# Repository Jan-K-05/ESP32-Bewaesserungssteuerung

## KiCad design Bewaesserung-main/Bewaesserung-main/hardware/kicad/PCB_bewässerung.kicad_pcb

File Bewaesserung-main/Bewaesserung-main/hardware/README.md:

# Hardware und PCB-Entwicklung

## Grundlage
Schaltplan und Leiterplattenlayout der Bewässerungssteuerung wurden mit KiCad erstellt. Die folgende Bauteilübersicht basiert auf der Stückliste (CSV) des aktuellen Leiterplattenprojekts.

| Bauteil | Anzahl | Wert / Typ |
|---|---:|---|
| Mikrocontroller | 1 | DFRobot FireBeetle 2 ESP32-E |
| Leistungstransistoren Q1–Q8 | 8 | IRLZ44N |
| Freilaufdioden D1–D8 | 8 | 1N4007 |
| Gate-Widerstände | 8 | 300 Ω |
| Weitere Widerstände | 10 + 1 + 1 | 10 kΩ, 20 kΩ, 47 kΩ |
| DC/DC-Wandler | 1 | TRACO TSR2-2450N |
| Sicherung | 1 | 5 A |
| Puffer-/Entstörkondensatoren | 6 | 4 × 100 nF, 470 µF / 25 V, 100 µF / 10 V |

Die GPIO-Zuordnung der aktuellen Firmware ist in [firmware/bewaesserung.yaml](../firmware/bewaesserung.yaml) dokumentiert. Frühere Pinbelegungen entsprechen nicht mehr dem aktuellen Stand.

## Sensoren
- RS12-Regensensor: GPIO36, invertiertes Digitalsignal
- YF-B7-Durchflusssensor: GPIO35, Impulsmessung; derzeit 660 Impulse/L als Näherungswert
- NTC-Wassertemperatur: GPIO34, ADC mit Widerstands- und NTC-Umrechnung

## Bilddokumentation

KiCad-Schaltplan

Leiterplattenlayout

Teilbestückter Prototyp – Vorderseite

Leiterplattenrückseite – nachträgliche Anpassung des Regensensorsignals

## Bestückungsstand und Anpassung des Regensensors

Die gefertigte Leiterplatte ist bislang teilweise bestückt. Der FireBeetle-Controller ist montiert; Spannungsversorgung und Sensoranschlüsse sind aufgebaut. Von acht vorgesehenen Ventilstufen ist bislang eine bestückt. Die vollständige Bestückung und die Prüfung unter realen Wasserdrücken stehen noch aus, da die Gartenleitungen und Verteiler noch nicht fertiggestellt sind.

Regensensor RS12: Bei der Inbetriebnahme wurde festgestellt, dass das Ausgangsverhalten des Sensors von der in der Anleitung beschriebenen Open-Collector-Schaltung abweicht. Da diese Abweichung bei den ersten Tests nicht erkannt wurde, war eine Anpassung der bereits gefertigten Leiterplatte erforderlich. Dazu wurde auf der Leiterplattenrückseite ein zusätzlicher Widerstand zwischen Regensignal und GND angebracht. Die Pegelanpassung an den ESP32 erfolgt über einen Spannungsteiler. Die elektrische Funktion dieser Anpassung wurde erfolgreich geprüft. Der zusätzliche Widerstand ist als dauerhafte Lösung vorgesehen; eine erneute Fertigung der Leiterplatte ist derzeit nicht geplant. Die Änderung ist auf dem Foto der Leiterplattenrückseite erkennbar und wurde noch nicht in die KiCad-Dateien übernommen.

## Entwicklungsablauf
1. Anforderungen an die Bewässerungszonen und die Ventillasten festlegen
2. Schaltplan und Bauteilauswahl in KiCad ausarbeiten
3. Leiterplattenlayout für Leistungs- und Sensorsignale erstellen
4. Leiterplatte fertigen lassen, teilweise bestücken und elektrisch prüfen
5. Controller mit ESPHome und Home Assistant verbinden

## Noch ausstehende Arbeiten

- Die restlichen sieben Ventilstufen bestücken und prüfen
- Den Durchflusssensor unter realen Bedingungen kalibrieren
- Die Temperaturmessung kalibrieren
- Die dauerhaft vorgesehene Anpassung des Regensensors in den KiCad-Dateien dokumentieren
- Die gesamte Bewässerung nach Fertigstellung der Gartenleitungen hydraulisch testen
- Die geplanten lokalen Sicherheitsfunktionen ergänzen und erproben

Die geplante ESP-NOW-Verbindung zu einem zusätzlichen Waveshare-ESP mit Ethernet-Anschluss ist in der [Projektübersicht](../README.md) beschrieben. Sie ist noch nicht umgesetzt.

Die KiCad-Quelldateien liegen direkt unter [kicad/](kicad/), darunter [Projekt](kicad/PCB_bewässerung.kicad_pro), [Schaltplan](kicad/PCB_bewässerung.kicad_sch), [PCB-Layout](kicad/PCB_bewässerung.kicad_pcb), Symbol- und Footprint-Bibliotheken sowie die [Originalstückliste](kicad/PCB_bewässerung.csv). Eine ergänzende [vereinfachte Stückliste](kicad/PCB_bewaesserung_BOM.csv) ist ebenfalls enthalten.

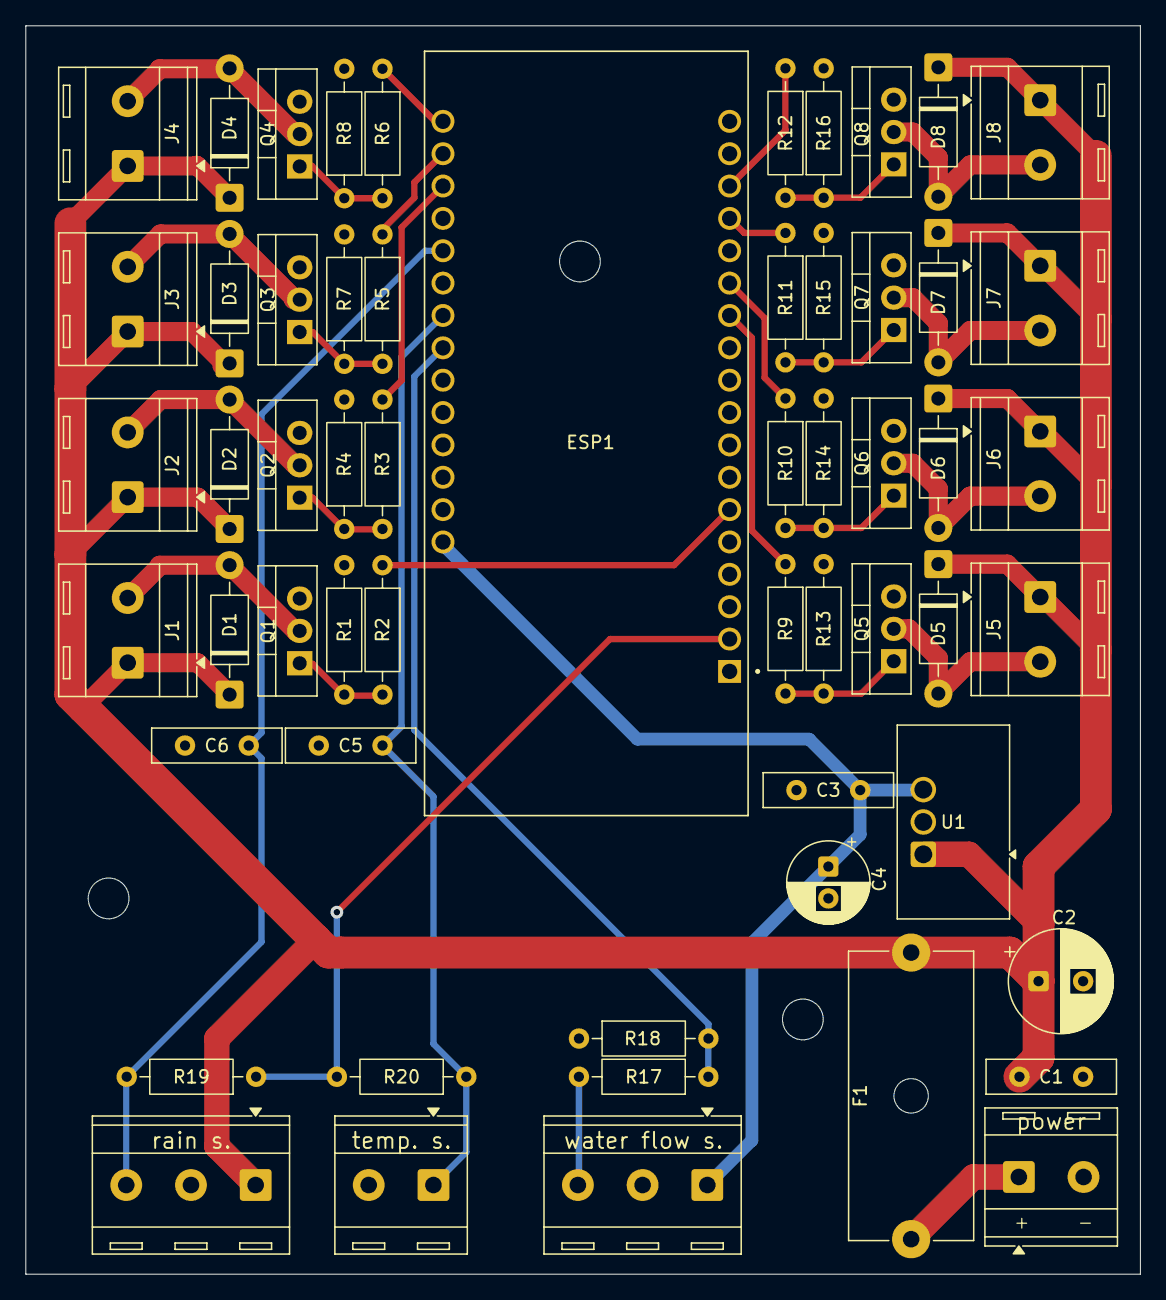
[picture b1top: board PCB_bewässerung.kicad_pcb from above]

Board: 2 copper layers, 87.5 x 98.0 mm, 57 parts (0 on the bottom side), 33 nets.

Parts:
C1, C3, C5, C6: 100nF; C_Disc_D10.0mm_W2.5mm_P5.00mm
C2: 470uF/25V; CP_Radial_D8.0mm_P3.50mm
C4: 100uF/10V; CP_Radial_D6.3mm_P2.50mm
D1, D2, D3, D4, D5, D6, D7, D8: 1N4007; D_DO-41_SOD81_P10.16mm_Horizontal
ESP1: DFR0654
F1: 5A; Fuseholder_Cylinder-5x20mm_Schurter_0031_8201_Horizontal_Op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
J1, J2, J3, J4, J5, J6, J7, J8, J9, J11: Screw_Terminal_01x02; TerminalBlock_RND_205-00287_1x02_P5.08mm_Horizontal
J12, J13: Screw_Terminal_01x03; TerminalBlock_RND_205-00288_1x03_P5.08mm_Horizontal
Q1, Q2, Q3, Q4, Q5, Q6, Q7, Q8: IRLZ44N; TO-220-3_Vertical
R1, R4, R7, R8, R13, R14, R15, R16, R19: 10kR; R_Axial_DIN0207_L6.3mm_D2.5mm_P10.16mm_Horizontal
R2, R3, R5, R6, R9, R10, R11, R12: 300R; R_Axial_DIN0207_L6.3mm_D2.5mm_P10.16mm_Horizontal
R17: 51kR; R_Axial_DIN0207_L6.3mm_D2.5mm_P10.16mm_Horizontal
R18: 68kR; R_Axial_DIN0207_L6.3mm_D2.5mm_P10.16mm_Horizontal
R20: 47kR; R_Axial_DIN0207_L6.3mm_D2.5mm_P10.16mm_Horizontal
U1: TSR2-2450N; Converter_DCDC_TRACO_TSR2-24xxN_TSR2-24xxxN_THT

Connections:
/3V3: ESP1.2 (3V3), R19.1, R20.2
/5V: C3.1, C4.1, ESP1.32 (VCC), J13.1, U1.3 (Vout)
/12V: C1.1, C2.1, D1.1 (K), D2.1 (K), D3.1 (K), D4.1 (K), D5.1 (K), D6.1 (K), D7.1 (K), D8.1 (K), F1.1, J1.1, J2.1, J3.1, J4.1, J5.1, J6.1, J7.1, J8.1, J12.1, U1.1 (Vin)
GND: C1.2, C2.2, C3.2, C4.2, C5.1, C6.1, ESP1.30 (GND), J9.2, J11.2, J12.2, J13.2, Q1.3 (S), Q2.3 (S), Q3.3 (S), Q4.3 (S), Q5.3 (S), Q6.3 (S), Q7.3 (S), Q8.3 (S), R1.2, R4.2, R7.2, R8.2, R13.2, R14.2, R15.2, R16.2, R18.1, U1.2 (GND)
unnamed: D1.2 (A), J1.2, Q1.2 (D)
unnamed: D2.2 (A), J2.2, Q2.2 (D)
unnamed: D3.2 (A), J3.2, Q3.2 (D)
unnamed: D4.2 (A), J4.2, Q4.2 (D)
unnamed: D5.2 (A), J5.2, Q5.2 (D)
unnamed: D6.2 (A), J6.2, Q6.2 (D)
unnamed: D7.2 (A), J7.2, Q7.2 (D)
unnamed: D8.2 (A), J8.2, Q8.2 (D)
unnamed: C6.2, ESP1.23 (A0), J12.3, R19.2
unnamed: C5.2, ESP1.25 (A2), J11.1, R20.1
unnamed: ESP1.26 (A3), R17.1, R18.2
unnamed: ESP1.16 (D2), R12.1
unnamed: ESP1.15 (D3), R11.1
unnamed: ESP1.13 (D6), R10.1
unnamed: ESP1.12 (D7), R9.1
unnamed: ESP1.19 (D10), R6.1
unnamed: ESP1.20 (D11), R5.1
unnamed: ESP1.21 (D12), R3.1
unnamed: ESP1.6 (SCK), R2.1
unnamed: F1.2, J9.1
unnamed: J13.3, R17.2
unnamed: Q1.1 (G), R1.1, R2.2
unnamed: Q2.1 (G), R3.2, R4.1
unnamed: Q3.1 (G), R5.2, R7.1
unnamed: Q4.1 (G), R6.2, R8.1
unnamed: Q5.1 (G), R9.2, R13.1
unnamed: Q6.1 (G), R10.2, R14.1
unnamed: Q7.1 (G), R11.2, R15.1
unnamed: Q8.1 (G), R12.2, R16.1

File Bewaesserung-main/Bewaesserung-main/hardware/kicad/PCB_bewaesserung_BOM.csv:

Reference,Qty,Value,Footprint
"C1,C3,C5,C6",4,100nF,Capacitor_THT:C_Disc_D10.0mm_W2.5mm_P5.00mm
C2,1,470uF/25V,Capacitor_THT:CP_Radial_D8.0mm_P3.50mm
C4,1,100uF/10V,Capacitor_THT:CP_Radial_D6.3mm_P2.50mm
"D1,D2,D3,D4,D5,D6,D7,D8",8,1N4007,Diode_THT:D_DO-41_SOD81_P10.16mm_Horizontal
ESP1,1,DFRobot FireBeetle 2 ESP32-E,FireBeetle_DFR0654:DFR0654
F1,1,5A,Fuse:Fuseholder_Cylinder-5x20mm_Schurter_0031_8201_Horizontal_Open
"J1,J2,J3,J4,J5,J6,J7,J8,J9,J11",10,Screw_Terminal_01x02,TerminalBlock_RND:TerminalBlock_RND_205-00287_1x02_P5.08mm_Horizontal
"J12,J13",2,Screw_Terminal_01x03,TerminalBlock_RND:TerminalBlock_RND_205-00288_1x03_P5.08mm_Horizontal
"Q1,Q2,Q3,Q4,Q5,Q6,Q7,Q8",8,IRLZ44N,Package_TO_SOT_THT:TO-220-3_Vertical
"R1,R4,R7,R8,R13,R14,R15,R16,R17,R19",10,10kR,Resistor_THT:R_Axial_DIN0207_L6.3mm_D2.5mm_P10.16mm_Horizontal
"R2,R3,R5,R6,R9,R10,R11,R12",8,300R,Resistor_THT:R_Axial_DIN0207_L6.3mm_D2.5mm_P10.16mm_Horizontal
R18,1,20kR,Resistor_THT:R_Axial_DIN0207_L6.3mm_D2.5mm_P10.16mm_Horizontal
R20,1,47kR,Resistor_THT:R_Axial_DIN0207_L6.3mm_D2.5mm_P10.16mm_Horizontal
U1,1,TSR2-2450N,Converter_DCDC:Converter_DCDC_TRACO_TSR2-24xxN_TSR2-24xxxN_THT
